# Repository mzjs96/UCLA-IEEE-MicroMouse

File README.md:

UCLA-IEEE-MicroMouse 2017

Code for Rat with nucleo board (STM32)
written with mbed.h

PCB and schematic design for the Mouse

To be continued.

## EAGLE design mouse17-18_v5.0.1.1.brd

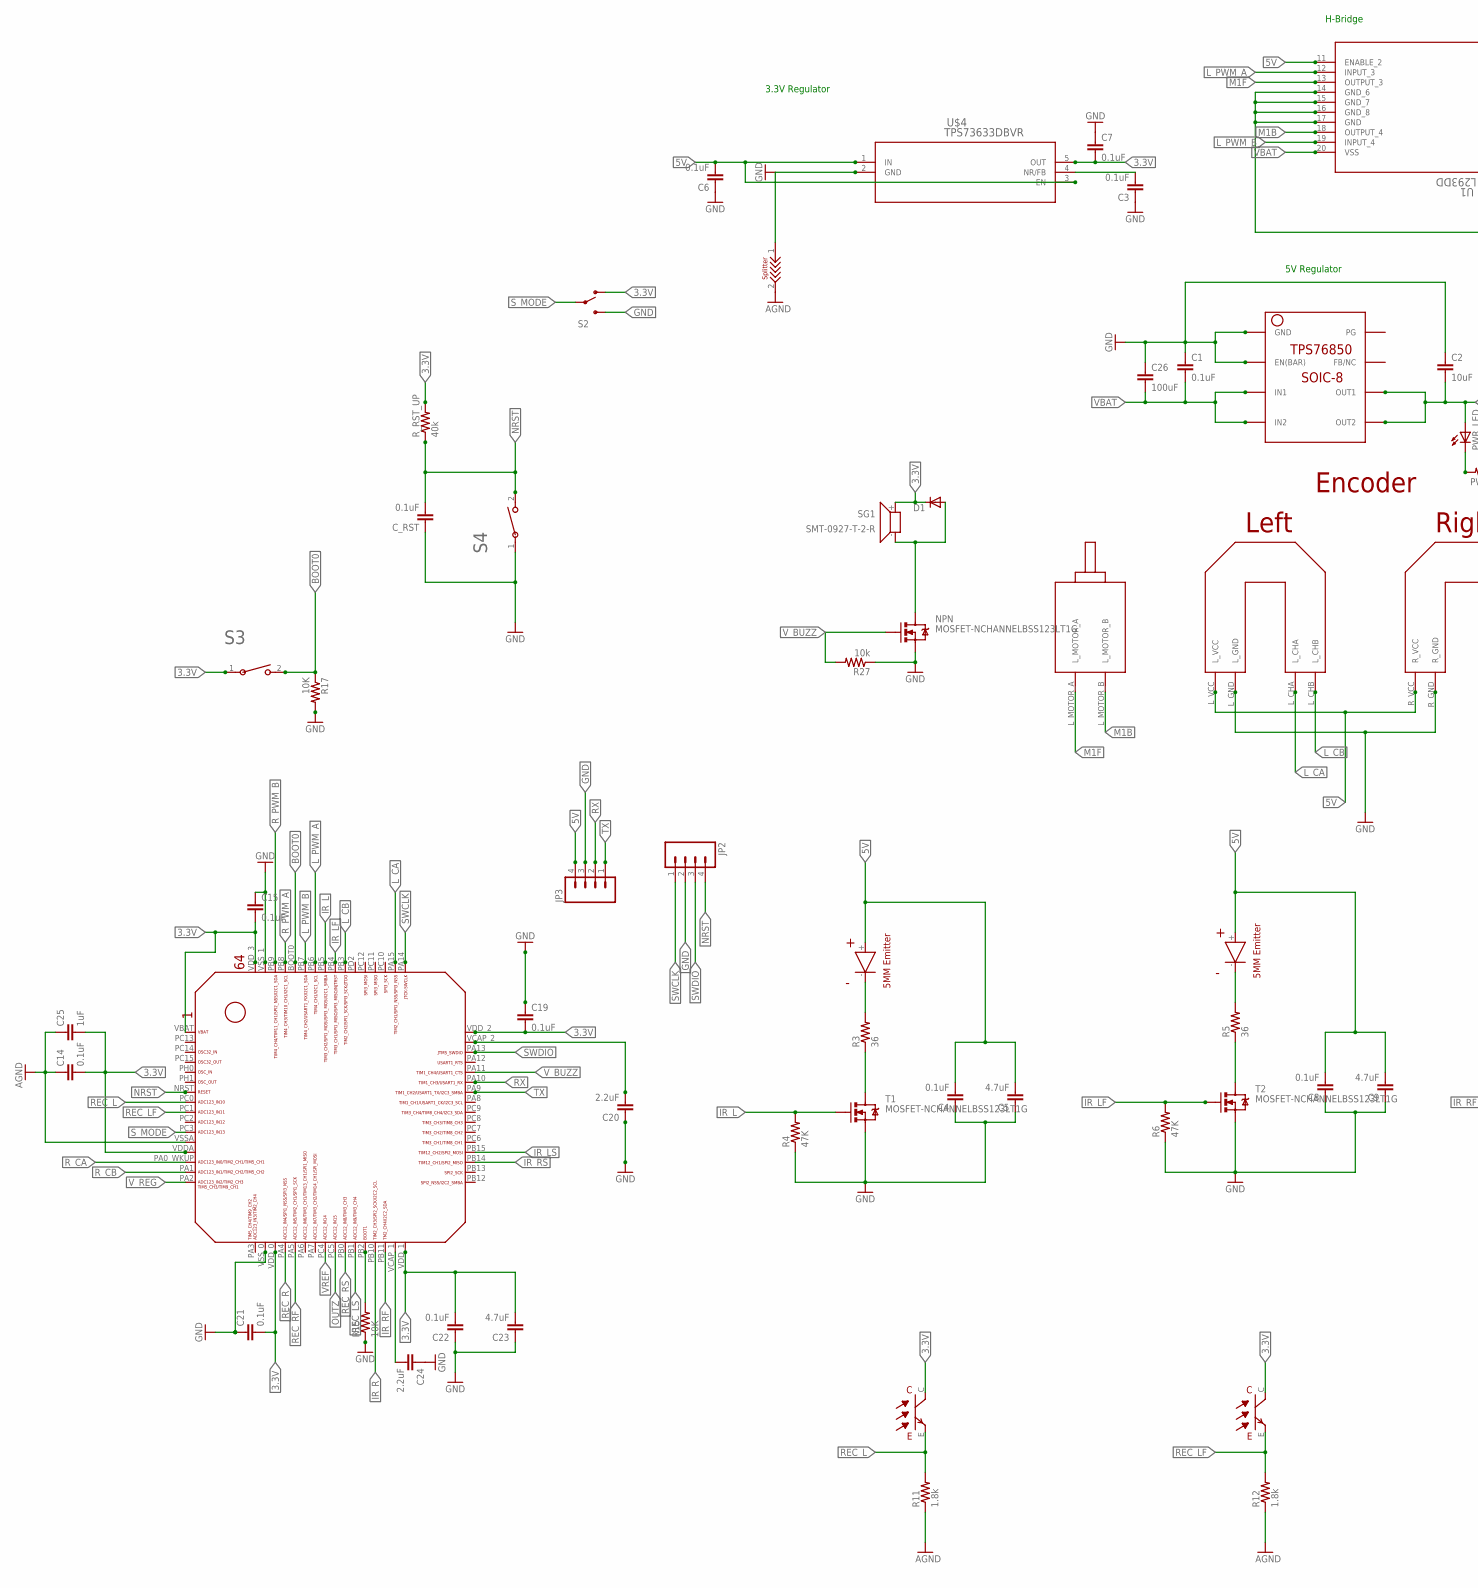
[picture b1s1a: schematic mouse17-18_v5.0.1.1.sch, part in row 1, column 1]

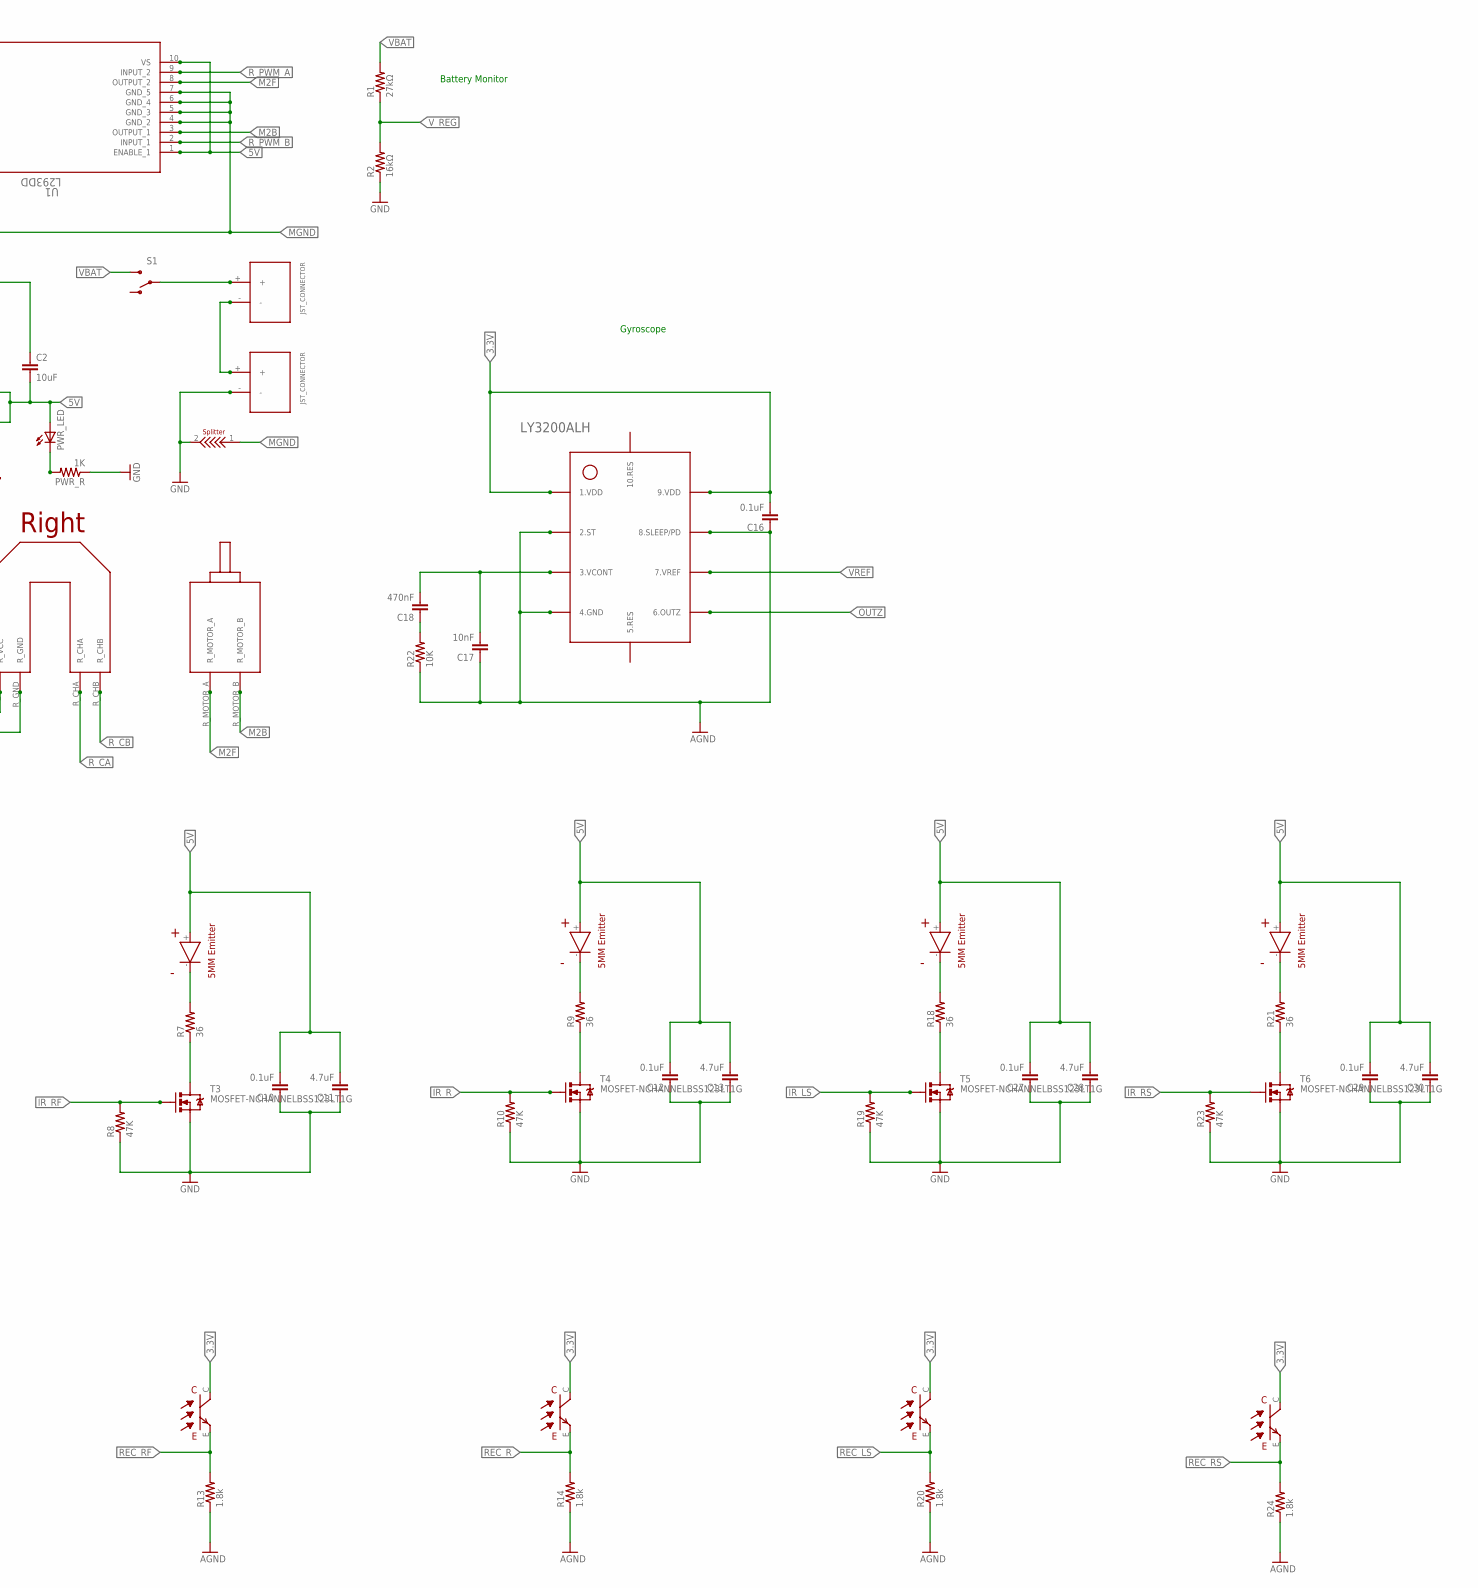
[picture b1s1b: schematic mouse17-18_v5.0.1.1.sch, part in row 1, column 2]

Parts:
C1: 0.1uF; 0805
C2: 10uF; 0805
C3, C6, C7: 0.1uF; C0603
C4, C8, C10, C12, C14, C15, C16, C19, C21, C22, C27, C29: 0.1uF; 0603-CAP
C5, C9, C11, C13, C23, C28, C30: 4.7uF; 0603-CAP
C17: 10nF; 0603-CAP
C18: 470nF; 0603-CAP
C20, C24: 2.2uF; 0603-CAP
C25: 1uF; 0603-CAP
C26: 100uF; C1210
C_RST: 0.1uF; 0603-CAP
D1: DIODESMA; SMA-DIODE
JP2, JP3: M04PTH; 1X04
NPN: MOSFET-NCHANNELBSS123LT1G; SOT23-3
PWR_LED: LED_ESML0603; LED_SML0603
PWR_R: 1K; 0805
R1: 27kΩ; 0805
R2: 16kΩ; 0805
R3, R5, R7, R9, R18, R21: 36; 0805
R4, R6, R8, R10, R19, R23: 47K; 0603-RES
R11, R12, R13, R14, R20, R24: 1.8k; 0603-RES
R15, R17, R22: 10K; 0603-RES
R27: 10k; 0603-RES
R_RST_UP: 40k; 0603-RES
S1: SWITCH-SPSTPTH; SWITCH-SPDT
S2: SWITCH-SPST-SMD-A
S3, S4: 1825965-1; SWDIP2_256X198P100
SG1: SMT-0927-T-2-R
T1, T2, T3, T4, T5, T6: MOSFET-NCHANNELBSS123LT1G; SOT23-3
U1: L293DD; SO-20
U$1: TPS76850(SOIC-8)
U$2, U$3: JST_CONNECTOR_FEMALE
U$4: TPS73633DBVR; DBV5
U$5: FUTURA_V1.0_MOTOR_MOUNT; FUTURA_V1.0_MOTOT_MOUNT
U$6, U$7, U$8, U$9, U$25, U$28: EMITTER
U$11, U$15, U$18, U$19, U$27, U$30: RECEIVER
U$13, U$22: SPLITTER
U$17: STM32F405/415_LQFP64
U$23: LY3200ALH

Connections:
3.3V: C7.2, C14.2, C15.2, C16.2, C19.2, C21.2, C22.2, C23.2, C25.2, D1.C, R_RST_UP.2, S2.1 (O), S3.1, SG1.+ (1), U$4.5 (OUT), U$11.C, U$15.C, U$17.VBAT, U$17.VDDA, U$17.VDD_0, U$17.VDD_1, U$17.VDD_2, U$17.VDD_3, U$18.C, U$19.C, U$23.1.VDD@1 (1.VDD), U$23.9.VDD@2 (9.VDD), U$27.C, U$30.C
5V: C2.2, C4.2, C5.2, C6.2, C8.2, C9.2, C10.2, C11.2, C12.2, C13.2, C27.2, C28.2, C29.2, C30.2, JP3.4, PWR_LED.A, U1.1 (ENABLE_1), U1.10 (VS), U1.11 (ENABLE_2), U$1.OUT1, U$1.OUT2, U$4.1 (IN), U$4.3 (EN), U$5.L_VCC, U$5.R_VCC, U$6.+, U$7.+, U$8.+, U$9.+, U$25.+, U$28.+
AGND: C14.1, C16.1, C17.1, C25.1, R11.1, R12.1, R13.1, R14.1, R20.1, R22.1, R24.1, U$13.2, U$17.VSSA, U$23.2.ST, U$23.4.GND, U$23.8.SLEEP/PD
BOOT0: R17.1, S3.2, U$17.BOOT0
GND: C1.1, C2.1, C3.1, C4.1, C5.1, C6.1, C7.1, C8.1, C9.1, C10.1, C11.1, C12.1, C13.1, C15.1, C19.1, C20.1, C21.1, C22.1, C23.1, C24.1, C26.1, C27.1, C28.1, C29.1, C30.1, C_RST.1, JP2.2, JP3.3, NPN.2 (S), PWR_R.1, R2.1, R4.1, R6.1, R8.1, R10.1, R15.1, R17.2, R19.1, R23.1, R27.1, S2.3 (S), S4.1, T1.2 (S), T2.2 (S), T3.2 (S), T4.2 (S), T5.2 (S), T6.2 (S), U$1.EN(BAR), U$1.GND, U$3.-, U$4.2 (GND), U$5.L_GND, U$5.R_GND, U$13.1, U$17.VSS_0, U$17.VSS_1, U$22.2
IR_L: R4.2, T1.1 (G), U$17.PB5
IR_LF: R6.2, T2.1 (G), U$17.PB4
IR_LS: R19.2, T5.1 (G), U$17.PB15
IR_R: R10.2, T4.1 (G), U$17.PB10
IR_RF: R8.2, T3.1 (G), U$17.PB11
IR_RS: R23.2, T6.1 (G), U$17.PB14
LED_L: R3.2, U$6.-
LED_LF: R5.2, U$7.-
LED_LS: R18.2, U$25.-
LED_R: R9.2, U$9.-
LED_RF: R7.2, U$8.-
LED_RS: R21.2, U$28.-
L_CA: U$5.L_CHA, U$17.PA15
L_CB: U$5.L_CHB, U$17.PB3
L_PWM_A: U1.12 (INPUT_3), U$17.PB6
L_PWM_B: U1.19 (INPUT_4), U$17.PB7
M1B: U1.18 (OUTPUT_4), U$5.L_MOTOR_B
M1F: U1.13 (OUTPUT_3), U$5.L_MOTOR_A
M2B: U1.3 (OUTPUT_1), U$5.R_MOTOR_B
M2F: U1.8 (OUTPUT_2), U$5.R_MOTOR_A
MGND: U1.4 (GND_2), U1.5 (GND_3), U1.6 (GND_4), U1.7 (GND_5), U1.14 (GND_6), U1.15 (GND_7), U1.16 (GND_8), U1.17 (GND), U$22.1
unnamed: S1.2, U$2.+
unnamed: U$2.-, U$3.+
unnamed: R5.1, T2.3 (D)
unnamed: D1.A, NPN.3 (D), SG1.- (2)
unnamed: R3.1, T1.3 (D)
unnamed: R7.1, T3.3 (D)
unnamed: R9.1, T4.3 (D)
unnamed: C17.2, C18.2, U$23.3.VCONT
unnamed: C3.2, U$4.4 (NR/FB)
unnamed: C20.2, U$17.VCAP_2
unnamed: C24.2, U$17.VCAP_1
unnamed: R15.2, U$17.PB2
unnamed: C18.1, R22.2
unnamed: PWR_LED.C, PWR_R.2
unnamed: R18.1, T5.3 (D)
unnamed: R21.1, T6.3 (D)
NRST: C_RST.2, JP2.4, R_RST_UP.1, S4.2, U$17.NRST
OUTZ: U$17.PC5, U$23.6.OUTZ
REC_L: R11.2, U$17.PC0, U$19.E
REC_LF: R12.2, U$17.PC1, U$18.E
REC_LS: R20.2, U$17.PB1, U$27.E
REC_R: R14.2, U$11.E, U$17.PA4
REC_RF: R13.2, U$15.E, U$17.PA5
REC_RS: R24.2, U$17.PB0, U$30.E
RX: JP3.2, U$17.PA10
R_CA: U$5.R_CHA, U$17.PA0_WKUP (PA0_AKUP)
R_CB: U$5.R_CHB, U$17.PA1
R_PWM_A: U1.9 (INPUT_2), U$17.PB8
R_PWM_B: U1.2 (INPUT_1), U$17.PB9
SWCLK: JP2.1, U$17.PA14
SWDIO: JP2.3, U$17.PA13
S_MODE: S2.2, U$17.PC3
TX: JP3.1, U$17.PA9
VBAT: C1.2, C26.2, R1.2, S1.3 (S), U1.20 (VSS), U$1.IN1, U$1.IN2
VREF: U$17.PC4, U$23.7.VREF
V_BUZZ: NPN.1 (G), R27.2, U$17.PA11
V_REG: R1.1, R2.2, U$17.PA2

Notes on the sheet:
3.3V Regulator
5V Regulator
H-Bridge
Battery Monitor
Gyroscope

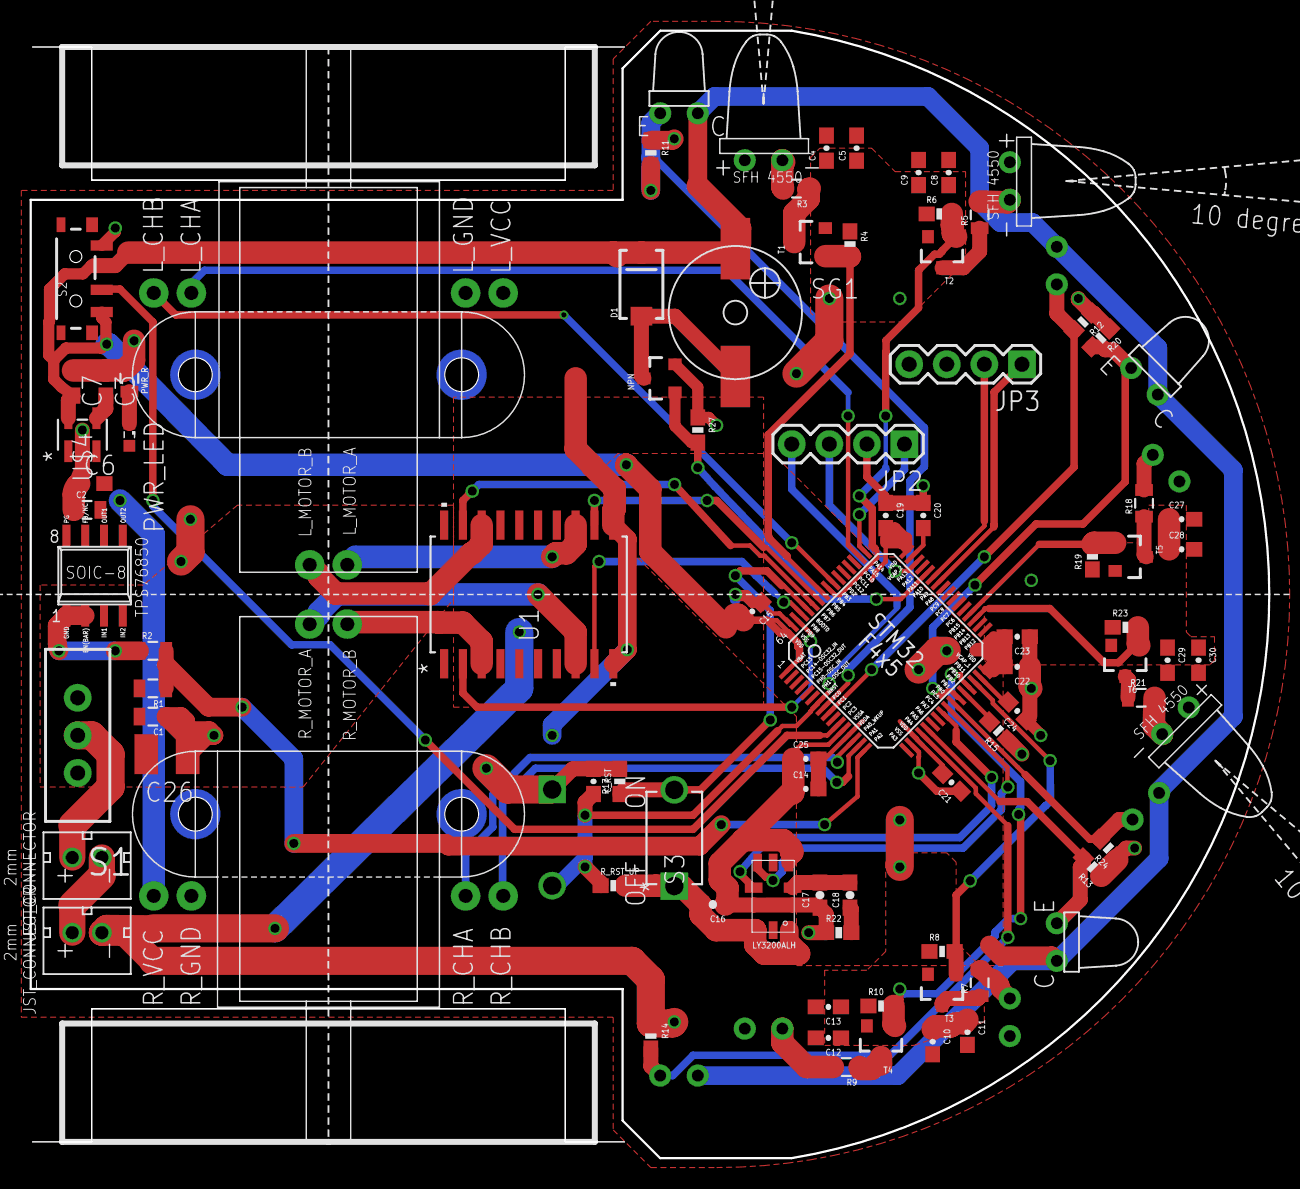
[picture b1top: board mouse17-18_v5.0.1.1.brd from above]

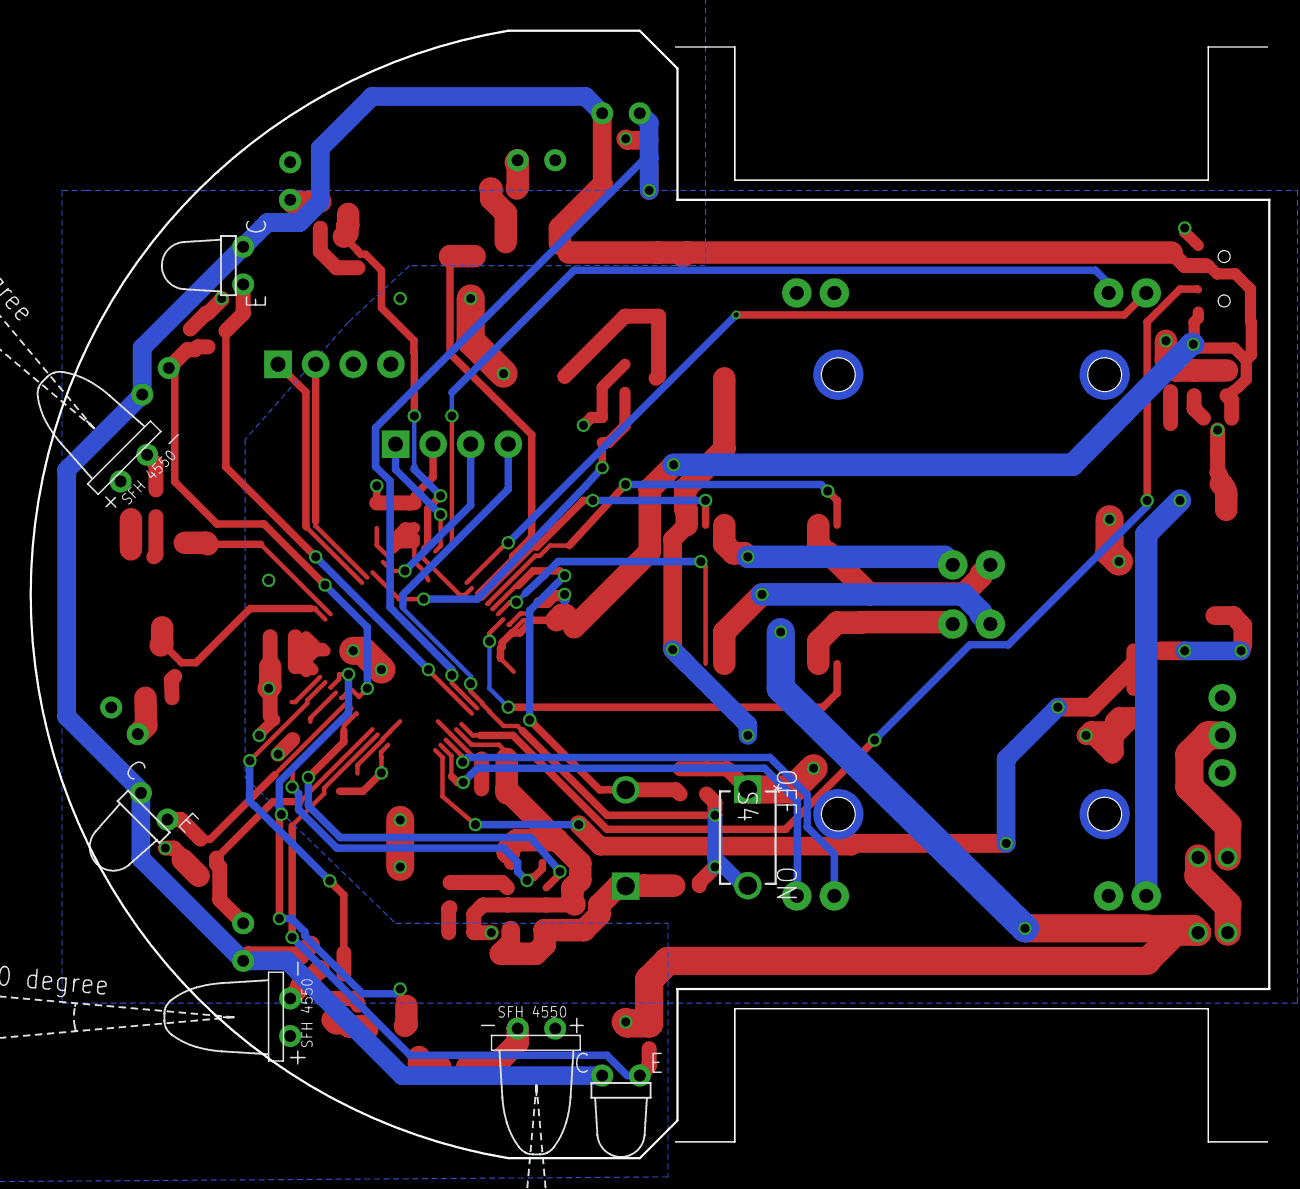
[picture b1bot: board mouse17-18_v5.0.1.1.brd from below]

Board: 2 copper layers, 83.7 x 76.2 mm, 95 parts (7 on the bottom side), 63 nets.

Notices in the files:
parts and their libraries:
SparkFun: Licensing: CC v3.0 Share-Alike You are welcome to use this library for commercial purposes.
SparkFun-Passives: Licensing: Creative Commons ShareAlike 4.0 International - https://creativecommons.org/licenses/by-sa/4.0
